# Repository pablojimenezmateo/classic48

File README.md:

# Classic 48
A custom 48 key split keyboard

# Bill Of Materials
| Name | Quantity/Variety | Item Price (€) | Shipping (€) | Link |
|--|--|--|--|--|
|Brown Choc Switches|70 pcs|47.59|0|[AliExpress](https://www.aliexpress.com/item/1005005883472162.html?spm=a2g0o.order_list.order_list_main.199.2613194dDxt0T9)|
|Choc Keycaps|10 x B type (5 pcs each)|20|4.86|[AliExpress](https://www.aliexpress.com/item/1005007966026757.html?spm=a2g0o.order_detail.order_detail_item.2.1a644d1apVQ3mB)|
|Choc Blind Keycaps|1 x E type (5 pcs each)|2.99|4.86|[AliExpress](https://www.aliexpress.com/item/1005007966026757.html?spm=a2g0o.order_detail.order_detail_item.2.1a644d1apVQ3mB)|
|Soldering iron|1|19.69|0|[AliExpress](https://www.aliexpress.com/item/4000019437594.html?spm=a2g0o.order_detail.order_detail_item.3.5b734d1aqwuhYo)|
|SK6812 Mini-E LEDs|1 (100 pcs)|3.49|0.09|[AliExpress](https://www.aliexpress.com/item/1005002865070175.html?spm=a2g0o.order_detail.order_detail_item.3.394a4d1aan5FQG)|
|RP2040 Pro Micro|2|6.38|0|[AliExpress](https://www.aliexpress.com/item/1005006787060405.html?spm=a2g0o.order_detail.order_detail_item.3.7ac54d1aTYXgAB)|
|TRRS|1 (10 pcs)|2.11|0|[AliExpress](https://www.aliexpress.com/item/33029465106.html?spm=a2g0o.order_detail.order_detail_item.3.4e99f19crF5m72)|
|Soldering mount|1|8.09|0|[AliExpress](https://www.aliexpress.com/item/1005007045716674.html?spm=a2g0o.order_detail.order_detail_item.3.382bf19cIL4kQU)|
|Flux pen|1|1.01|0|[AliExpress](https://www.aliexpress.com/item/1005007346959832.html?spm=a2g0o.order_detail.order_detail_item.3.742df19cndnLH3)|
|Choc Hot Swap Sockets|1 x Type B (70 pcs)|5.89|0|[AliExpress](https://www.aliexpress.com/item/1005007232040760.html?spm=a2g0o.order_detail.order_detail_item.3.55faf19c1tKr8g)|
|SMD diode|1 1N4148W SOD123 (100 pcs)|1.08|0|[AliExpress](https://www.aliexpress.com/item/1005005707644429.html?spm=a2g0o.order_detail.order_detail_item.3.1c9df19csikjkj)|
|Multimeter|1|3.65|0|[AliExpress](https://www.aliexpress.com/item/1005007059884308.html?spm=a2g0o.order_detail.order_detail_item.3.1676f19c6qa6g1)|
|Desoldering braid|1 x 1.5mm 1.5m|1.59|0|[AliExpress](https://www.aliexpress.com/item/1005005398523384.html?spm=a2g0o.order_list.order_list_main.138.26131802A570A7)|
|Round female pin header|1 (10 pcs)|3.59|0.81|[AliExpress](https://www.aliexpress.com/item/33036413973.html?spm=a2g0o.order_detail.order_detail_item.3.7ef1f19cFHvYfp)|
|Round male pin header|1 (5 pcs)|2.00|1.31|[AliExpress](https://www.aliexpress.com/item/1005008053808682.html?spm=a2g0o.order_detail.order_detail_item.3.244ff19cC2E150)|
|PCB|1 (5 pcs)|10.26| 15.87 (shipping) + 29.14 (customs + handling fees DHL)|[JLCPCB](https://jlcpcb.com/)|

Grand total: **196.35 €**

# Installing the kicad libaries
1. Go to KiCad, `Preferences` -> `Configure Paths`, add new row with name `PJIMENEZ` and path to `pjimenez.kicad`
2. Go to KiCad, `Preferences` -> `Manage Footprint Libraries`, add new row with name `pjimenez` and path to `pjimenez.kicad/pjimenez.pretty`
3. Go to KiCad, `Preferences` -> `Manage Symbol Libraries`, add new row with name `pjimenez` and path to `pjimenez.kicad/pjimenez.kicad_sym`

# Firmware
Checkout the [classic48-keymap repository](https://github.com/pablojimenezmateo/classic48-keymap)

# License
This project is licensed under Creative commons Attribution 3.0 Unported, more info : http://creativecommons.org/licenses/by/3.0/deed.en_US

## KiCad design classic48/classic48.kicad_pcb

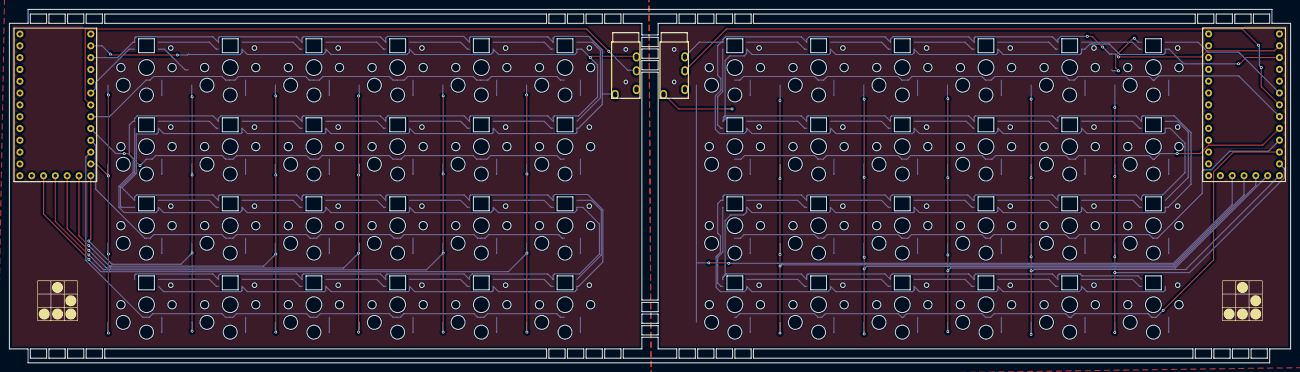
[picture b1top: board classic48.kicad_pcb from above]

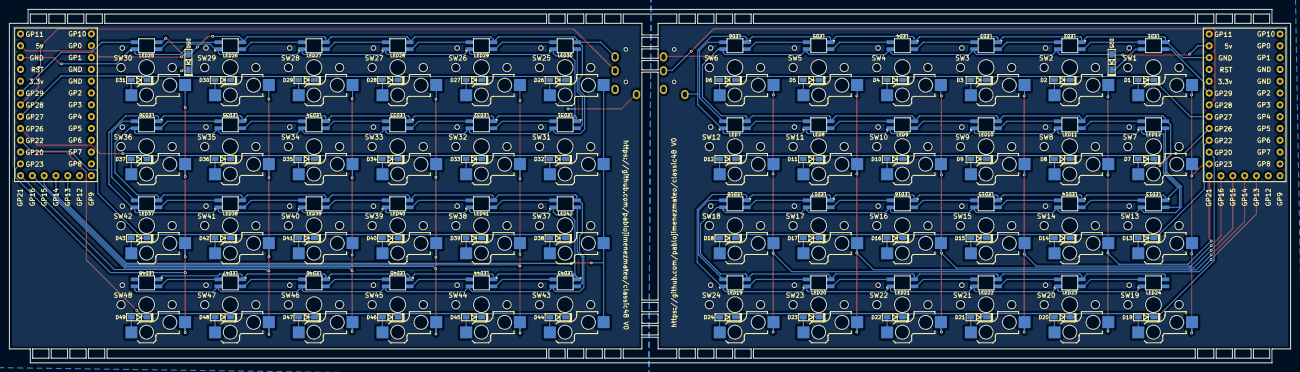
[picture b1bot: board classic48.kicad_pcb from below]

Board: 2 copper layers, 275.4 x 75.9 mm, 150 parts (50 on the bottom side), 124 nets.

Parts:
D1, D2, D3, D4, D5, D6, D7, D8, D9, D10, D11, D12, D13, D14, D15, D16, D17, D18, D19, D20, D21, D22, D23, D24, D25, D26, D27, D28, D29, D30, D31, D32, D33, D34, D35, D36, D37, D38, D39, D40, D41, D42, D43, D44, D45, D46, D47, D48, D49, D50: Diode_1N4148-SOD123
LED1, LED2, LED3, LED4, LED5, LED6, LED7, LED8, LED9, LED10, LED11, LED12, LED13, LED14, LED15, LED16, LED17, LED18, LED19, LED20, LED21, LED22, LED23, LED24, LED25, LED26, LED27, LED28, LED29, LED30, LED31, LED32, LED33, LED34, LED35, LED36, LED37, LED38, LED39, LED40, LED41, LED42, LED43, LED44, LED45, LED46, LED47, LED48: LED_SK6812MINI-E; LED_SK6812-MINI-E
SW1, SW2, SW3, SW4, SW5, SW6, SW7, SW8, SW9, SW10, SW11, SW12, SW13, SW14, SW15, SW16, SW17, SW18, SW19, SW20, SW21, SW22, SW23, SW24, SW25, SW26, SW27, SW28, SW29, SW30, SW31, SW32, SW33, SW34, SW35, SW36, SW37, SW38, SW39, SW40, SW41, SW42, SW43, SW44, SW45, SW46, SW47, SW48: Switch; Switch_ChocV1-hotswap
U1, U3: RP2040_Pro_Micro
U2, U4: TRRS; TRRS_PJ-320A

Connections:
5V Left: D25.2 (A), LED2.1 (VDD), LED3.1 (VDD), LED4.1 (VDD), LED5.1 (VDD), LED6.1 (VDD), LED7.1 (VDD), LED8.1 (VDD), LED9.1 (VDD), LED10.1 (VDD), LED11.1 (VDD), LED12.1 (VDD), LED13.1 (VDD), LED14.1 (VDD), LED15.1 (VDD), LED16.1 (VDD), LED17.1 (VDD), LED18.1 (VDD), LED19.1 (VDD), LED20.1 (VDD), LED21.1 (VDD), LED22.1 (VDD), LED23.1 (VDD), LED24.1 (VDD), U1.30 (5v), U2.4 (RING2)
5V Right: D50.2 (A), LED26.1 (VDD), LED27.1 (VDD), LED28.1 (VDD), LED29.1 (VDD), LED30.1 (VDD), LED31.1 (VDD), LED32.1 (VDD), LED33.1 (VDD), LED34.1 (VDD), LED35.1 (VDD), LED36.1 (VDD), LED37.1 (VDD), LED38.1 (VDD), LED39.1 (VDD), LED40.1 (VDD), LED41.1 (VDD), LED42.1 (VDD), LED43.1 (VDD), LED44.1 (VDD), LED45.1 (VDD), LED46.1 (VDD), LED47.1 (VDD), LED48.1 (VDD), U3.30 (5v), U4.4 (RING2)
Col 0 Left: SW1.2, SW7.2, SW13.2, SW19.2, U1.20 (GP23)
Col 0 Right: SW30.2, SW36.2, SW42.2, SW48.2, U3.20 (GP23)
Col 1 Left: SW2.2, SW8.2, SW14.2, SW20.2, U1.19 (GP21)
Col 1 Right: SW29.2, SW35.2, SW41.2, SW47.2, U3.19 (GP21)
Col 2 Left: SW3.2, SW9.2, SW15.2, SW21.2, U1.18 (GP16)
Col 2 Right: SW28.2, SW34.2, SW40.2, SW46.2, U3.18 (GP16)
Col 3 Left: SW4.2, SW10.2, SW16.2, SW22.2, U1.17 (GP15)
Col 3 Right: SW27.2, SW33.2, SW39.2, SW45.2, U3.17 (GP15)
Col 4 Left: SW5.2, SW11.2, SW17.2, SW23.2, U1.16 (GP14)
Col 4 Right: SW26.2, SW32.2, SW38.2, SW44.2, U3.16 (GP14)
Col 5 Left: SW6.2, SW12.2, SW18.2, SW24.2, U1.15 (GP13)
Col 5 Right: SW25.2, SW31.2, SW37.2, SW43.2, U3.15 (GP13)
GND Left: LED1.3 (VSS), LED2.3 (VSS), LED3.3 (VSS), LED4.3 (VSS), LED5.3 (VSS), LED6.3 (VSS), LED7.3 (VSS), LED8.3 (VSS), LED9.3 (VSS), LED10.3 (VSS), LED11.3 (VSS), LED12.3 (VSS), LED13.3 (VSS), LED14.3 (VSS), LED15.3 (VSS), LED16.3 (VSS), LED17.3 (VSS), LED18.3 (VSS), LED19.3 (VSS), LED20.3 (VSS), LED21.3 (VSS), LED22.3 (VSS), LED23.3 (VSS), LED24.3 (VSS), U1.29 (GND), U2.1 (SLEEVE)
GND Right: LED25.3 (VSS), LED26.3 (VSS), LED27.3 (VSS), LED28.3 (VSS), LED29.3 (VSS), LED30.3 (VSS), LED31.3 (VSS), LED32.3 (VSS), LED33.3 (VSS), LED34.3 (VSS), LED35.3 (VSS), LED36.3 (VSS), LED37.3 (VSS), LED38.3 (VSS), LED39.3 (VSS), LED40.3 (VSS), LED41.3 (VSS), LED42.3 (VSS), LED43.3 (VSS), LED44.3 (VSS), LED45.3 (VSS), LED46.3 (VSS), LED47.3 (VSS), LED48.3 (VSS), U3.29 (GND), U4.1 (SLEEVE)
LED Data Left: LED1.4 (DIN), U1.26 (GP29)
LED data Right: LED25.4 (DIN), U3.26 (GP29)
unnamed: D1.2 (A), SW1.1
unnamed: D2.2 (A), SW2.1
unnamed: D3.2 (A), SW3.1
unnamed: D4.2 (A), SW4.1
unnamed: D5.2 (A), SW5.1
unnamed: D6.2 (A), SW6.1
unnamed: D7.2 (A), SW7.1
unnamed: D8.2 (A), SW8.1
unnamed: D9.2 (A), SW9.1
unnamed: D10.2 (A), SW10.1
unnamed: D11.2 (A), SW11.1
unnamed: D12.2 (A), SW12.1
unnamed: D13.2 (A), SW13.1
unnamed: D14.2 (A), SW14.1
unnamed: D15.2 (A), SW15.1
unnamed: D16.2 (A), SW16.1
unnamed: D17.2 (A), SW17.1
unnamed: D18.2 (A), SW18.1
unnamed: D19.2 (A), SW19.1
unnamed: D20.2 (A), SW20.1
unnamed: D21.2 (A), SW21.1
unnamed: D22.2 (A), SW22.1
unnamed: D23.2 (A), SW23.1
unnamed: D24.2 (A), SW24.1
unnamed: D25.1 (K), LED1.1 (VDD)
unnamed: D26.2 (A), SW25.1
unnamed: D27.2 (A), SW26.1
unnamed: D28.2 (A), SW27.1
unnamed: D29.2 (A), SW28.1
unnamed: D30.2 (A), SW29.1
unnamed: D31.2 (A), SW30.1
unnamed: D32.2 (A), SW31.1
unnamed: D33.2 (A), SW32.1
unnamed: D34.2 (A), SW33.1
unnamed: D35.2 (A), SW34.1
unnamed: D36.2 (A), SW35.1
unnamed: D37.2 (A), SW36.1
unnamed: D38.2 (A), SW37.1
unnamed: D39.2 (A), SW38.1
unnamed: D40.2 (A), SW39.1
unnamed: D41.2 (A), SW40.1
unnamed: D42.2 (A), SW41.1
unnamed: D43.2 (A), SW42.1
unnamed: D44.2 (A), SW43.1
unnamed: D45.2 (A), SW44.1
unnamed: D46.2 (A), SW45.1
unnamed: D47.2 (A), SW46.1
unnamed: D48.2 (A), SW47.1
unnamed: D49.2 (A), SW48.1
unnamed: D50.1 (K), LED25.1 (VDD)
unnamed: LED1.2 (DOUT), LED2.4 (DIN)
unnamed: LED2.2 (DOUT), LED3.4 (DIN)
unnamed: LED3.2 (DOUT), LED4.4 (DIN)
unnamed: LED4.2 (DOUT), LED5.4 (DIN)
unnamed: LED5.2 (DOUT), LED6.4 (DIN)
unnamed: LED6.2 (DOUT), LED7.4 (DIN)
unnamed: LED7.2 (DOUT), LED8.4 (DIN)
unnamed: LED8.2 (DOUT), LED9.4 (DIN)
unnamed: LED9.2 (DOUT), LED10.4 (DIN)
unnamed: LED10.2 (DOUT), LED11.4 (DIN)
unnamed: LED11.2 (DOUT), LED12.4 (DIN)
unnamed: LED12.2 (DOUT), LED13.4 (DIN)
unnamed: LED13.2 (DOUT), LED14.4 (DIN)
unnamed: LED14.2 (DOUT), LED15.4 (DIN)
unnamed: LED15.2 (DOUT), LED16.4 (DIN)
unnamed: LED16.2 (DOUT), LED17.4 (DIN)
unnamed: LED17.2 (DOUT), LED18.4 (DIN)
unnamed: LED18.2 (DOUT), LED19.4 (DIN)
unnamed: LED19.2 (DOUT), LED20.4 (DIN)
unnamed: LED20.2 (DOUT), LED21.4 (DIN)
unnamed: LED21.2 (DOUT), LED22.4 (DIN)
unnamed: LED22.2 (DOUT), LED23.4 (DIN)
unnamed: LED23.2 (DOUT), LED24.4 (DIN)
unnamed: LED25.2 (DOUT), LED26.4 (DIN)
unnamed: LED26.2 (DOUT), LED27.4 (DIN)
unnamed: LED27.2 (DOUT), LED28.4 (DIN)
unnamed: LED28.2 (DOUT), LED29.4 (DIN)
unnamed: LED29.2 (DOUT), LED30.4 (DIN)
unnamed: LED30.2 (DOUT), LED31.4 (DIN)
unnamed: LED31.2 (DOUT), LED32.4 (DIN)
unnamed: LED32.2 (DOUT), LED33.4 (DIN)
unnamed: LED33.2 (DOUT), LED34.4 (DIN)
unnamed: LED34.2 (DOUT), LED35.4 (DIN)
unnamed: LED35.2 (DOUT), LED36.4 (DIN)
unnamed: LED36.2 (DOUT), LED37.4 (DIN)
unnamed: LED37.2 (DOUT), LED38.4 (DIN)
unnamed: LED38.2 (DOUT), LED39.4 (DIN)
unnamed: LED39.2 (DOUT), LED40.4 (DIN)
unnamed: LED40.2 (DOUT), LED41.4 (DIN)
unnamed: LED41.2 (DOUT), LED42.4 (DIN)
unnamed: LED42.2 (DOUT), LED43.4 (DIN)
unnamed: LED43.2 (DOUT), LED44.4 (DIN)
unnamed: LED44.2 (DOUT), LED45.4 (DIN)
unnamed: LED45.2 (DOUT), LED46.4 (DIN)
unnamed: LED46.2 (DOUT), LED47.4 (DIN)
unnamed: LED47.2 (DOUT), LED48.4 (DIN)
Row 0 Left: D1.1 (K), D2.1 (K), D3.1 (K), D4.1 (K), D5.1 (K), D6.1 (K), U1.24 (GP27)
Row 0 Right: D26.1 (K), D27.1 (K), D28.1 (K), D29.1 (K), D30.1 (K), D31.1 (K), U3.24 (GP27)
Row 1 Left: D7.1 (K), D8.1 (K), D9.1 (K), D10.1 (K), D11.1 (K), D12.1 (K), U1.23 (GP26)
Row 1 Right: D32.1 (K), D33.1 (K), D34.1 (K), D35.1 (K), D36.1 (K), D37.1 (K), U3.23 (GP26)
Row 2 Left: D13.1 (K), D14.1 (K), D15.1 (K), D16.1 (K), D17.1 (K), D18.1 (K), U1.22 (GP22)
Row 2 Right: D38.1 (K), D39.1 (K), D40.1 (K), D41.1 (K), D42.1 (K), D43.1 (K), U3.22 (GP22)
Row 3 Left: D19.1 (K), D20.1 (K), D21.1 (K), D22.1 (K), D23.1 (K), D24.1 (K), U1.21 (GP20)
Row 3 Right: D44.1 (K), D45.1 (K), D46.1 (K), D47.1 (K), D48.1 (K), D49.1 (K), U3.21 (GP20)
Serial data Left: U1.25 (GP28), U2.3 (RING1)
Serial data Right: U3.25 (GP28), U4.3 (RING1)

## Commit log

2025-02-02 Placeholder
2025-02-02 feat: libraries tested
2025-02-02 feat: add license to README
2025-02-02 chore: backup
2025-02-08 feat: schematic for left side
2025-02-08 feat: position all right side diodes
2025-02-08 fix: bring diodes to background
2025-02-08 feat: all LEDs in place
2025-02-08 chore: remove soldered 3D models
2025-02-08 feat: add GND marker to 6812
2025-02-08 feat: LED Vcc
2025-02-08 feat: LEDs and TRRS fully connected
2025-02-08 feat: finish tracks
2025-02-09 fix: DRC errors except LEDS
2025-02-09 feat: improve silk screen pin placement for 2040
2025-02-12 fix: left side LEDs were connected incorrectly feat: right side schema
2025-02-24 fix: LED connections
2025-02-24 chore: savefiles
2025-02-27 feat: right switches positions
2025-02-27 feat: LED and switch positions
2025-02-27 feat: position MCU and TRRS
2025-03-02 feat: fully wired
2025-03-14 wip: working on the cuts
2025-03-26 feat: add structure
2025-03-26 feat: add graphics
2025-03-26 feat: fill zone and export
2025-03-26 feat: sent to print
2025-07-11 feat: add image
2025-07-12 feat: add BOM
2025-07-31 feat: add keymap URL
